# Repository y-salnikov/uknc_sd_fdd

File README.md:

# uknc_sd_fdd
Контроллер дисковода для УКНЦ (МС0511), использующий образы дисков на SD-карте.
Сайт проекта: http://y-salnikov.github.io/uknc_sd_fdd/

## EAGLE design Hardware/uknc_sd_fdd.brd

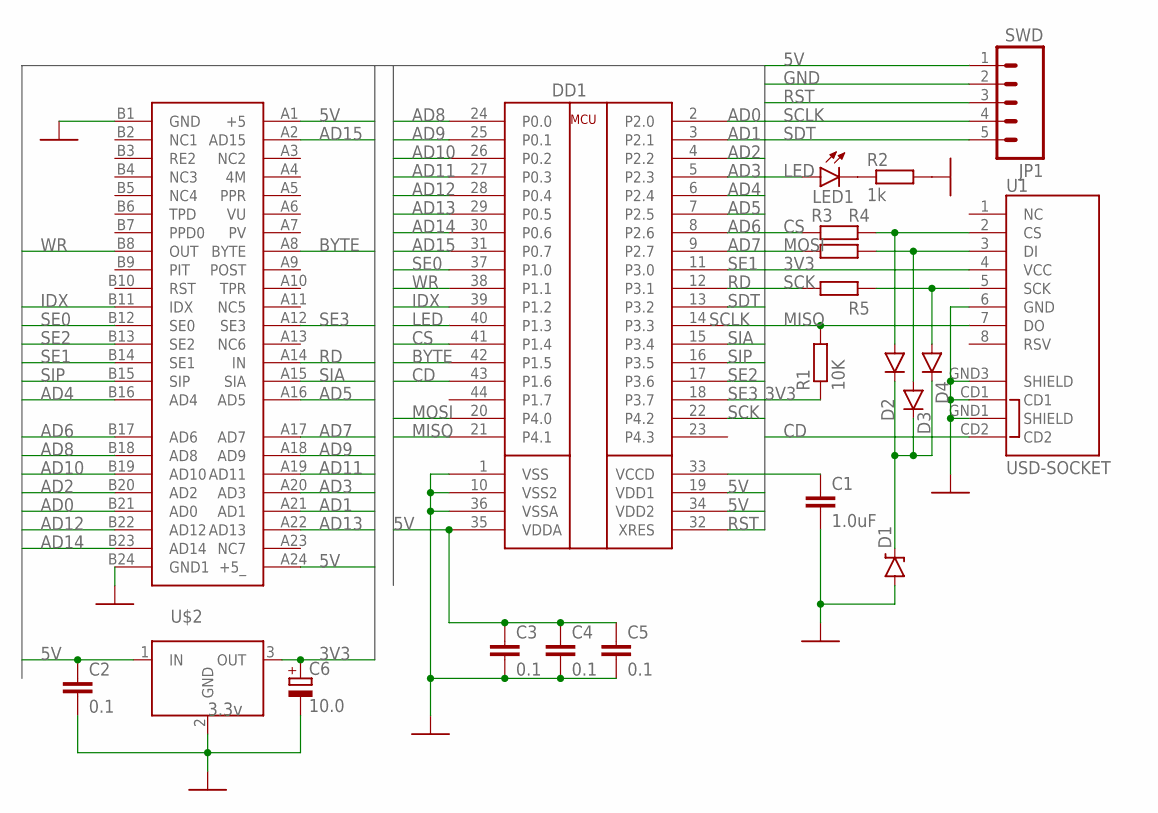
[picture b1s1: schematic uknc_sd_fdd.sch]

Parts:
C1: 1.0uF; 0805-CAP
C2, C3, C4, C5: 0.1; C0805
C6: 10.0; E1,8-4
D1: DIODE-ZENERPTH; DIODE-ZENER
D2, D3, D4: DIODEPTH; DIODE-1N4001
DD1: CY8C4245AXI; TQFP-44
JP1: SWD; 1X05
LED1: LED1206; LED-1206
R1: 10K; M0805
R2: 1k; R0805
R3, R4, R5: R-EU_R0805; R0805
U1: USD-SOCKET; MICROSD_1:1
U$1: SNP; SNP15-48-BOARD
U$2: 3.3v; 1235B

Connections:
3V3: C6.+, R1.1, U1.4 (VCC), U$2.3 (OUT)
5V: C2.1, C3.1, C4.1, C5.1, DD1.19 (VDD1), DD1.34 (VDD2), DD1.35 (VDDA), JP1.1, U$1.A1 (+5), U$1.A24 (+5_), U$2.1 (IN)
AD0: DD1.2 (P2.0), U$1.B21 (AD0)
AD1: DD1.3 (P2.1), U$1.A21 (AD1)
AD2: DD1.4 (P2.2), U$1.B20 (AD2)
AD3: DD1.5 (P2.3), U$1.A20 (AD3)
AD4: DD1.6 (P2.4), U$1.B16 (AD4)
AD5: DD1.7 (P2.5), U$1.A16 (AD5)
AD6: DD1.8 (P2.6), U$1.B17 (AD6)
AD7: DD1.9 (P2.7), U$1.A17 (AD7)
AD8: DD1.24 (P0.0), U$1.B18 (AD8)
AD9: DD1.25 (P0.1), U$1.A18 (AD9)
AD10: DD1.26 (P0.2), U$1.B19 (AD10)
AD11: DD1.27 (P0.3), U$1.A19 (AD11)
AD12: DD1.28 (P0.4), U$1.B22 (AD12)
AD13: DD1.29 (P0.5), U$1.A22 (AD13)
AD14: DD1.30 (P0.6), U$1.B23 (AD14)
AD15: DD1.31 (P0.7), U$1.A2 (AD15)
BYTE: DD1.42 (P1.5), U$1.A8 (BYTE)
CD: DD1.43 (P1.6), U1.CD2
CS: DD1.41 (P1.4), R3.1
GND: C1.2, C2.2, C3.2, C4.2, C5.2, C6.-, D1.P$2 (A), DD1.1 (VSS), DD1.10 (VSS2), DD1.36 (VSSA), JP1.2, R2.2, U1.6 (GND), U1.CD1, U1.GND1 (SHIELD), U1.GND3 (SHIELD), U$1.B1 (GND), U$1.B24 (GND1), U$2.2 (GND)
IDX: DD1.39 (P1.2), U$1.B11 (IDX)
LED: DD1.40 (P1.3), LED1.A
MISO: DD1.21 (P4.1), R1.2, U1.7 (DO)
MOSI: DD1.20 (P4.0), R4.1
unnamed: C1.1, DD1.33 (VCCD)
unnamed: D1.P$1 (C), D2.C, D3.C, D4.C
unnamed: LED1.C, R2.1
unnamed: D2.A, R3.2, U1.2 (CS)
unnamed: D3.A, R4.2, U1.3 (DI)
unnamed: D4.A, R5.2, U1.5 (SCK)
RD: DD1.12 (P3.1), U$1.A14 (IN)
RST: DD1.32 (XRES), JP1.3
SCK: DD1.22 (P4.2), R5.1
SCLK: DD1.14 (P3.3), JP1.4
SDT: DD1.13 (P3.2), JP1.5
SE0: DD1.37 (P1.0), U$1.B12 (SE0)
SE1: DD1.11 (P3.0), U$1.B14 (SE1)
SE2: DD1.17 (P3.6), U$1.B13 (SE2)
SE3: DD1.18 (P3.7), U$1.A12 (SE3)
SIA: DD1.15 (P3.4), U$1.A15 (SIA)
SIP: DD1.16 (P3.5), U$1.B15 (SIP)
WR: DD1.38 (P1.1), U$1.B8 (OUT)

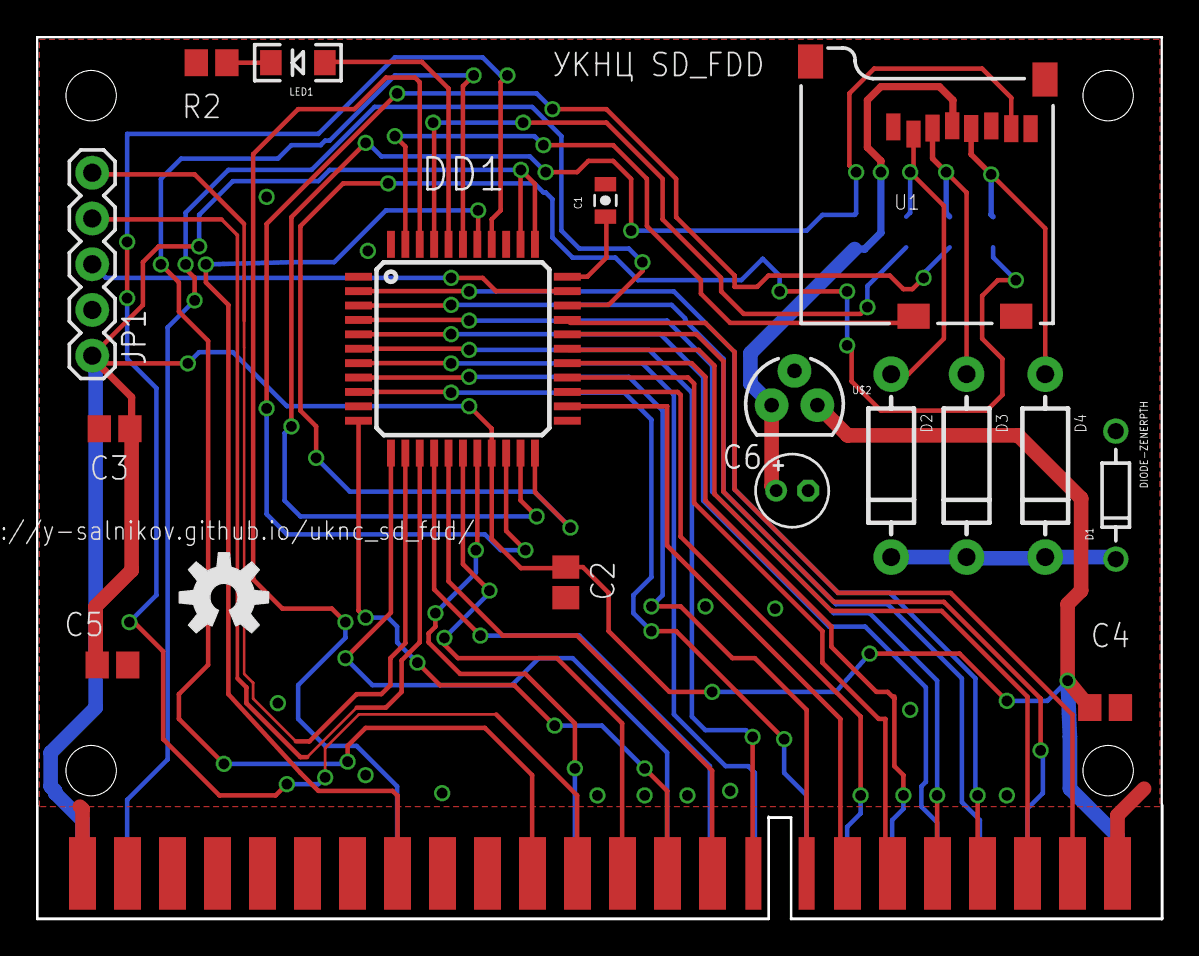
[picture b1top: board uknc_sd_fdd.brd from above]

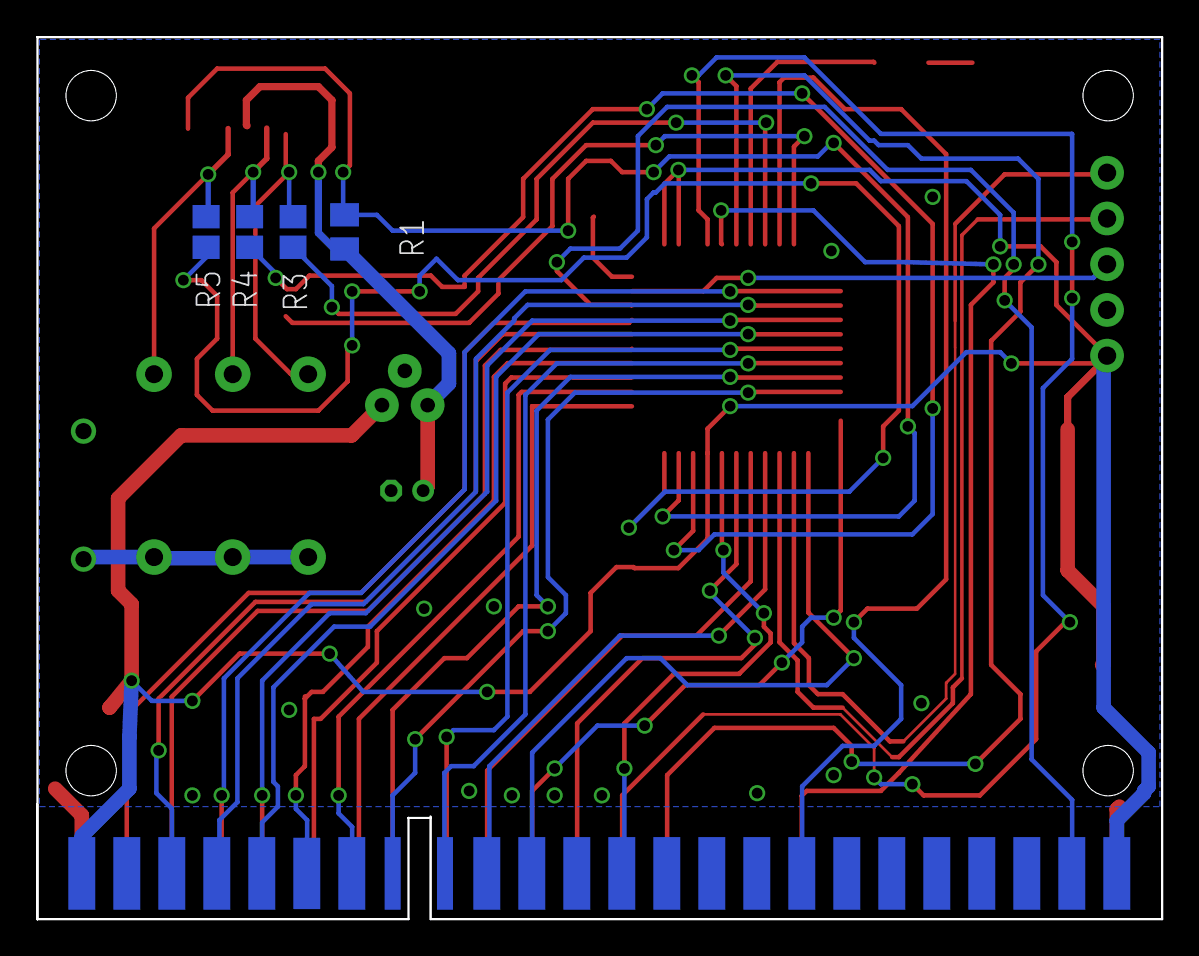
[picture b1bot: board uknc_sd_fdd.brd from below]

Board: 2 copper layers, 62.5 x 49.0 mm, 22 parts (4 on the bottom side), 44 nets.

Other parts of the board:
U$10: OSHW-LOGO-M

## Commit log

2015-08-31 создание репозитория
2015-08-31 замена симлинков файлами
2015-08-31 сайт проекта
2015-08-31 сайт
2015-09-01 hard and some soft
2015-09-01 debugging
2015-09-02 add syntax highlighting
2015-09-02 обновление поста
2015-09-04 обновил пост
2015-09-05 исправлена схема
2015-09-10 update post
2015-09-13 плата
2015-10-07 пришли платы
2015-10-10 add SD change detection
2015-10-10 добавил ссылку на сайт
2015-12-13 листинг прошивки в pdf
2016-01-30 Добавлен эмулятор кассеты ПЗУ
2016-01-30 add image
2016-02-21 disable network interrupts in firmware
2016-03-04 Заглушки на прерывания во время загрузки
2016-03-07 обновлен файл прошивки
2016-03-15 add kitprog photo
2016-03-15 supress warning
2016-03-15 Исправления для kramdown
2016-03-17 Отладка
2016-03-18 cleanup
2016-03-18 Добавлено сообщение об ошибке чтения загрузочного сектора
2016-08-01 alternative firmware
2017-02-04 Add link to Hobots archive
2017-03-13 Исправил SD на microSD
2017-03-24 Добавлен boot.mac
2017-07-13 Исправление некоторых опечаток, добавление ссылки

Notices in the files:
parts and their libraries:
SparkFun-DiscreteSemi: Licensing: Creative Commons ShareAlike 4.0 International - https://creativecommons.org/licenses/by-sa/4.0
